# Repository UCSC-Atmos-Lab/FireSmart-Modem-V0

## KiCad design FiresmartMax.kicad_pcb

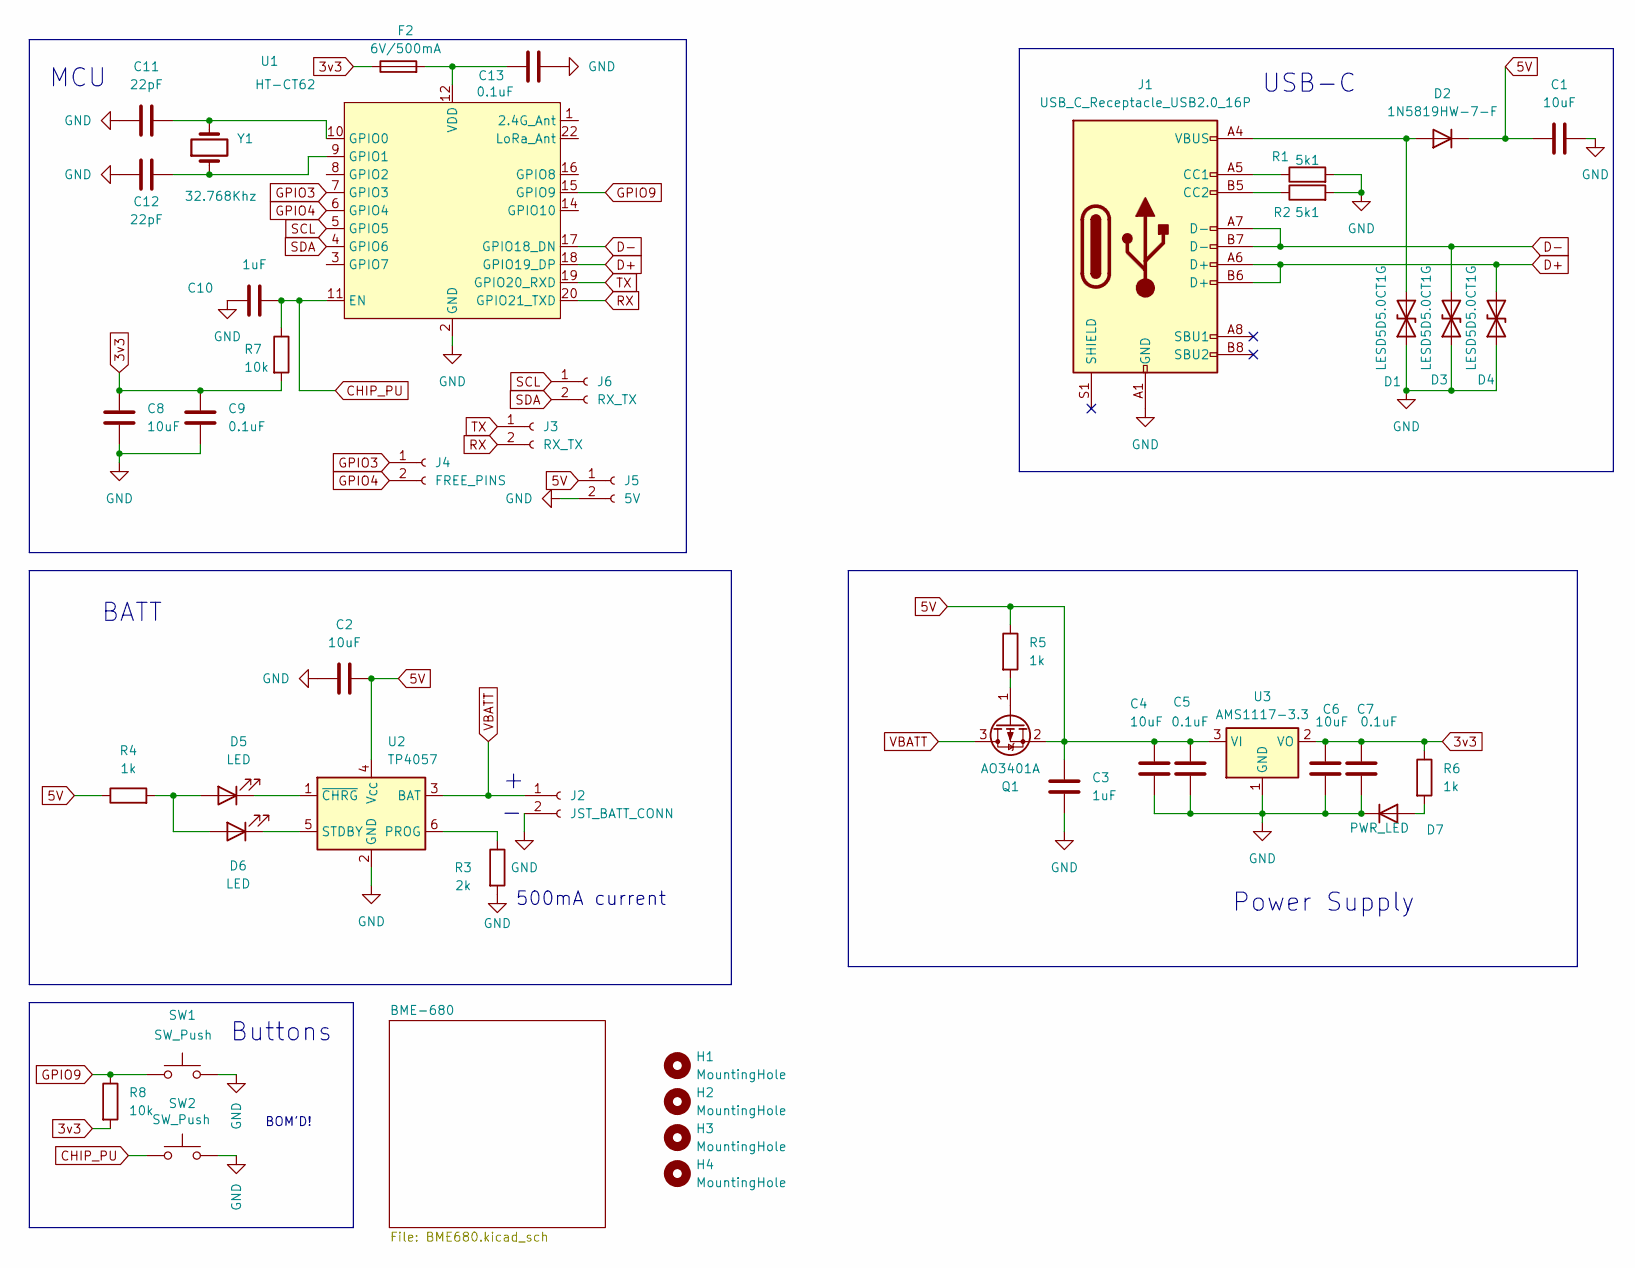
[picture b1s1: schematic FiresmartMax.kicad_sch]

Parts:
C1, C2, C4, C6, C8: 10uF; C_0805_2012Metric
C3, C10: 1uF; C_0805_2012Metric
C5, C7, C9, C13: 0.1uF; C_0201_0603Metric
C11, C12: 22pF; C_1206_3216Metric_Pad1.33x1.80mm_HandSolder
D1, D3, D4: LESD5D5.0CT1G; D_SOD-523
D2: 1N5819HW-7-F; D_SOD-123
D5, D6: LED; LED_1206_3216Metric_Pad1.42x1.75mm_HandSolder
D7: PWR_LED; D_0805_2012Metric_Pad1.15x1.40mm_HandSolder
F2: 6V/500mA; Fuse_1206_3216Metric_Pad1.42x1.75mm_HandSolder
H1, H2, H3, H4: MountingHole; MountingHole_2.7mm_M2.5_Pad_Via
J1: USB_C_Receptacle_USB2.0_16P; USB_C_Receptacle_HCTL_HC-TYPE-C-16P-01A
J2: JST_BATT_CONN; JST_PH_B2B-PH-K_1x02_P2.00mm_Vertical
J3, J6: RX_TX; JST_PH_B2B-PH-K_1x02_P2.00mm_Vertical
J4: FREE_PINS; JST_PH_B2B-PH-K_1x02_P2.00mm_Vertical
J5: 5V; JST_PH_B2B-PH-K_1x02_P2.00mm_Vertical
Q1: AO3401A; SOT-23
R1, R2: 5k1; R_0201_0603Metric
R3: 2k; R_1206_3216Metric_Pad1.30x1.75mm_HandSolder
R4: 1k; R_1206_3216Metric
R5, R6: 1k; R_1206_3216Metric_Pad1.30x1.75mm_HandSolder
R7, R8: 10k; R_0201_0603Metric
SW1, SW2: SW_Push; SW_SPST_Omron_B3FS-100xP
U1: HT-CT62; Heltec_HT-CT62
U2: TP4057; TSOT-23-6
U3: AMS1117-3.3; SOT-223-3_TabPin2
Y1: 32.768Khz; Crystal_SMD_2012-2Pin_2.0x1.2mm_HandSoldering

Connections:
3v3: C6.2, C7.1, C8.1, C9.1, F2.1, R6.1, R7.2, R8.2, U3.2 (VO); also elsewhere on the board
5V: C1.2, C2.2, C3.1, C4.2, C5.1, D2.1 (K), J5.1, Q1.2 (S), R4.1, R5.1, U2.4 (V_{CC}), U3.3 (VI)
CHIP_PU: C10.2, R7.1, SW2.1, U1.11 (EN)
D+: D4.2 (A2), J1.A6 (D+), J1.B6 (D+), U1.18 (GPIO19_DP)
D-: D3.2 (A2), J1.A7 (D-), J1.B7 (D-), U1.17 (GPIO18_DN)
GND: C1.1, C2.1, C3.2, C4.1, C5.2, C6.1, C7.2, C8.2, C9.2, C10.1, C11.1, C12.1, C13.1, D1.1 (A1), D3.1 (A1), D4.1 (A1), D7.1 (K), J1.A1 (GND), J1.A12 (GND), J1.B1 (GND), J1.B12 (GND), J2.2, J5.2, R1.2, R2.2, R3.2, SW1.2, SW2.2, U1.2 (GND), U1.13 (GND), U1.21 (GND), U2.2 (GND), U3.1 (GND); also elsewhere on the board
GPIO3: J4.1, U1.7 (GPIO3)
GPIO4: J4.2, U1.6 (GPIO4)
GPIO9: R8.1, SW1.1, U1.15 (GPIO9)
unnamed: D1.2 (A2), D2.2 (A), J1.A4 (VBUS), J1.A9 (VBUS), J1.B4 (VBUS), J1.B9 (VBUS)
unnamed: D5.2 (A), D6.2 (A), R4.2
unnamed: D5.1 (K), U2.1 (~CHRG)
unnamed: D6.1 (K), U2.5 (STDBY)
unnamed: D7.2 (A), R6.2
unnamed: J1.A5 (CC1), R1.1
unnamed: J1.B5 (CC2), R2.1
unnamed: Q1.1 (G), R5.2
unnamed: C11.2, U1.10 (GPIO0), Y1.2
unnamed: C12.2, U1.9 (GPIO1), Y1.1
unnamed: C13.2, F2.2, U1.12 (VDD)
unnamed: R3.1, U2.6 (PROG)
RX: J3.2, U1.20 (GPIO21_TXD)
SCL: J6.1, U1.5 (GPIO5); also elsewhere on the board
SDA: J6.2, U1.4 (GPIO6); also elsewhere on the board
TX: J3.1, U1.19 (GPIO20_RXD)
VBATT: J2.1, Q1.3 (D), U2.3 (BAT)

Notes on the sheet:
Power Supply
USB-C
BATT
Buttons
500mA current
BOM'D!
MCU

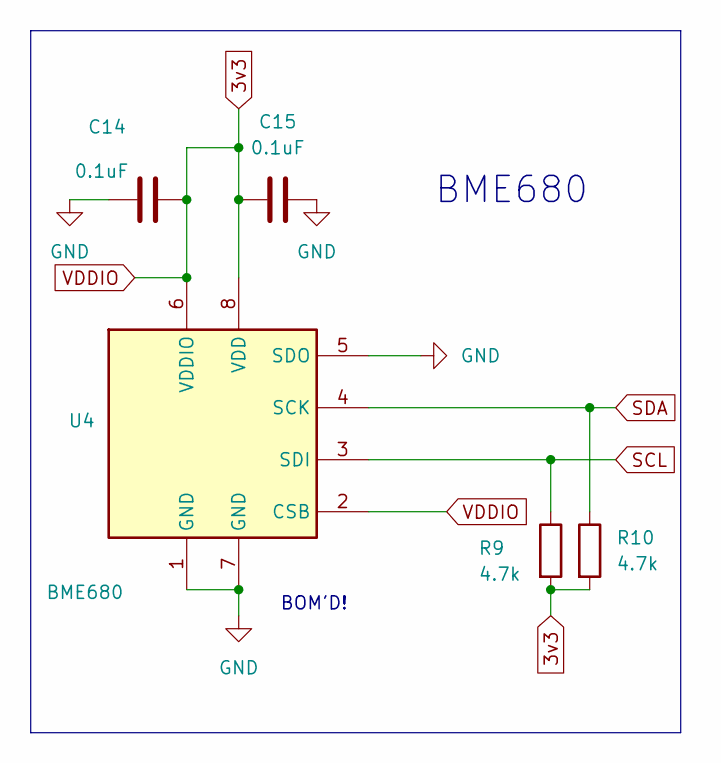
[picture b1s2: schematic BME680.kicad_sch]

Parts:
C14, C15: 0.1uF; C_0201_0603Metric
R9, R10: 4.7k; R_0201_0603Metric
U4: BME680; Bosch_LGA-8_3x3mm_P0.8mm_ClockwisePinNumbering

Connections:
3v3: C14.2, C15.1, R9.2, R10.2, U4.2 (CSB), U4.6 (VDDIO), U4.8 (VDD); also elsewhere on the board
GND: C14.1, C15.2, U4.1 (GND), U4.5 (SDO), U4.7 (GND); also elsewhere on the board
SCL: R9.1, U4.3 (SDI); also elsewhere on the board
SDA: R10.1, U4.4 (SCK); also elsewhere on the board

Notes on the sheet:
BOM'D!
BME680

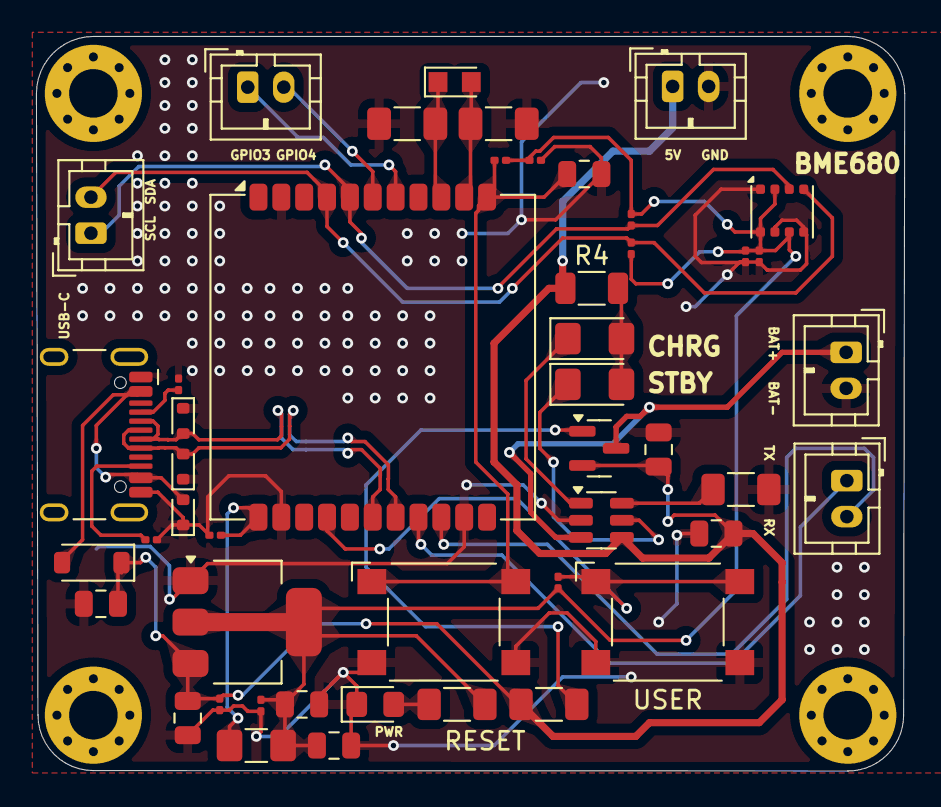
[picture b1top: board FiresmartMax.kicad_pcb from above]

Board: 2 copper layers, 48.2 x 40.8 mm, 51 parts (0 on the bottom side), 26 nets.

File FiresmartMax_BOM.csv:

"Id;""Designator"";""Footprint"";""Quantity"";""Designation"";""Supplier and ref"";",,,,,
"1;""R2","R1"";""R_0201_0603Metric"";2;""5k1"";;;",,,,
"2;""C6",C1,C2,C4,"C8"";""C_0805_2012Metric"";5;""10uF"";;;",
"3;""F2"";""Fuse_1206_3216Metric_Pad1.42x1.75mm_HandSolder"";1;""6V/500mA"";;;",,,,,
"4;""R5","R6"";""R_1206_3216Metric_Pad1.30x1.75mm_HandSolder"";2;""1k"";;;",,,,
"5;""C14",C5,C7,C9,C15,"C13"";""C_0201_0603Metric"";6;""0.1uF"";;;"
"6;""U1"";""Heltec_HT-CT62"";1;""HT-CT62"";;;",,,,,
"7;""R7","R8"";""R_0201_0603Metric"";2;""10k"";;;",,,,
"8;""R10","R9"";""R_0201_0603Metric"";2;""4.7k"";;;",,,,
"9;""SW2","USER"";""SW_SPST_Omron_B3FS-100xP"";2;""SW_Push"";;;",,,,
"10;""D7"";""D_0805_2012Metric_Pad1.15x1.40mm_HandSolder"";1;""PWR_LED"";;;",,,,,
"11;""D4",D3,"D1"";""D_SOD-523"";3;""LESD5D5.0CT1G"";;;",,,
"12;""U4"";""Bosch_LGA-8_3x3mm_P0.8mm_ClockwisePinNumbering"";1;""BME680"";;;",,,,,
"13;""Y1"";""Crystal_SMD_2012-2Pin_2.0x1.2mm_HandSoldering"";1;""32.768Khz"";;;",,,,,
"14;""C10","C3"";""C_0805_2012Metric"";2;""1uF"";;;",,,,
"15;""J3"";""JST_PH_B2B-PH-K_1x02_P2.00mm_Vertical"";1;""RX_TX"";;;",,,,,
"16;""R4"";""R_0402_1005Metric_Pad0.72x0.64mm_HandSolder"";1;""1k"";;;",,,,,
"17;""J1"";""USB_C_Receptacle_HCTL_HC-TYPE-C-16P-01A"";1;""USB_C_Receptacle_USB2.0_16P"";;;",,,,,
"18;""J2"";""JST_PH_B2B-PH-K_1x02_P2.00mm_Vertical"";1;""JST_BATT_CONN"";;;",,,,,
"19;""D6","D5"";""LED_1206_3216Metric_Pad1.42x1.75mm_HandSolder"";2;""LED"";;;",,,,
"20;""C11","C12"";""C_1206_3216Metric_Pad1.33x1.80mm_HandSolder"";2;""22pF"";;;",,,,
"21;""U3"";""SOT-223-3_TabPin2"";1;""AMS1117-3.3"";;;",,,,,
"22;""Q1"";""SOT-23"";1;""AO3401A"";;;",,,,,
"23;""J5"";""JST_PH_B2B-PH-K_1x02_P2.00mm_Vertical"";1;""5V"";;;",,,,,
"24;""D2"";""D_SOD-123"";1;""1N5819HW-7-F"";;;",,,,,
"25;""J4"";""JST_PH_B2B-PH-K_1x02_P2.00mm_Vertical"";1;""FREE_PINS"";;;",,,,,
"26;""U2"";""TSOT-23-6"";1;""TP4057"";;;",,,,,
"27;""R3"";""R_1206_3216Metric_Pad1.30x1.75mm_HandSolder"";1;""2k"";;;",,,,,

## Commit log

2025-07-04 Initial Upload
2025-10-10 Added Custom Serial Test
2025-10-11 Serial Tests Updated and Working
2025-10-17 Custom meshtastic firmware files added
